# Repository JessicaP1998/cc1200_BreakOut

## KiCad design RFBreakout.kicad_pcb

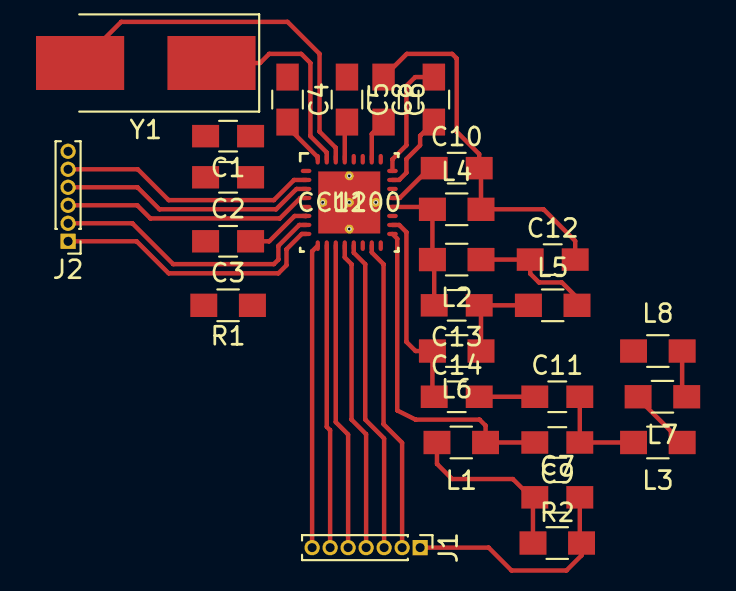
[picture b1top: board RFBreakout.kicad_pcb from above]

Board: 2 copper layers, 28 parts (0 on the bottom side), 32 nets.

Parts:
C1, C2, C3, C4, C5, C6, C7, C8, C9, C10, C11, C12, C13, C14: C; C_0805_HandSoldering
J1: Conn_01x07_Male; Pin_Header_Straight_1x07_Pitch1.00mm
J2: Conn_01x06_Male; Pin_Header_Straight_1x06_Pitch1.00mm
L1, L2, L3, L4, L5, L6, L7, L8: L; L_0805_HandSoldering
R1, R2: R; R_0805_HandSoldering
U1: CC1200; CC1200RHBR
Y1: Crystal; Crystal_SMD_7050-2pin_7.0x5.0mm_HandSoldering

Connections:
AVDD_IF: J1.3, U1.13
AVDD_RF: J1.2, U1.15
CSn: J1.5, U1.11
DVDD: J1.4, U1.12
GND: C1.2, C2.2, C3.2, C4.1, C5.1, C6.1, C10.2, C12.2, J2.6, L4.2, R1.2
GPIO0: J1.6, U1.10
GPIO2: J2.3, U1.4
GPIO3: J2.4, U1.3
unnamed: C3.1, U1.6
unnamed: C4.2, U1.32
unnamed: C5.2, U1.29
unnamed: C6.2, U1.26
unnamed: C7.1, L1.2, R2.1
unnamed: C8.1, U1.23
unnamed: C8.2, U1.24
unnamed: C9.2, L1.1, U1.17
unnamed: C10.1, U1.21
unnamed: C11.1, C14.2, L3.1, L7.2
unnamed: C9.1, C11.2, L3.2
unnamed: C12.1, L2.1, L5.2, U1.19
unnamed: C13.1, L5.1, L6.1
unnamed: C13.2, L2.2, L4.1, U1.20
unnamed: C14.1, L6.2, U1.18
unnamed: L7.1, L8.2
unnamed: R1.1, U1.14
unnamed: U1.30, Y1.2
unnamed: U1.31, Y1.1
RESET: J2.5, U1.2
SCLK: J2.1, U1.8
SI: J2.2, U1.7
SO: J1.7, U1.9
Vdd: C1.1, C2.1, C7.2, J1.1, R2.2, U1.1, U1.5, U1.22, U1.25, U1.27, U1.28

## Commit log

2019-01-24 Current edition of CC1200 breakout

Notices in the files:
parts and their libraries:
Copyright 2016 Accelerated Designs. All rights reserved.
